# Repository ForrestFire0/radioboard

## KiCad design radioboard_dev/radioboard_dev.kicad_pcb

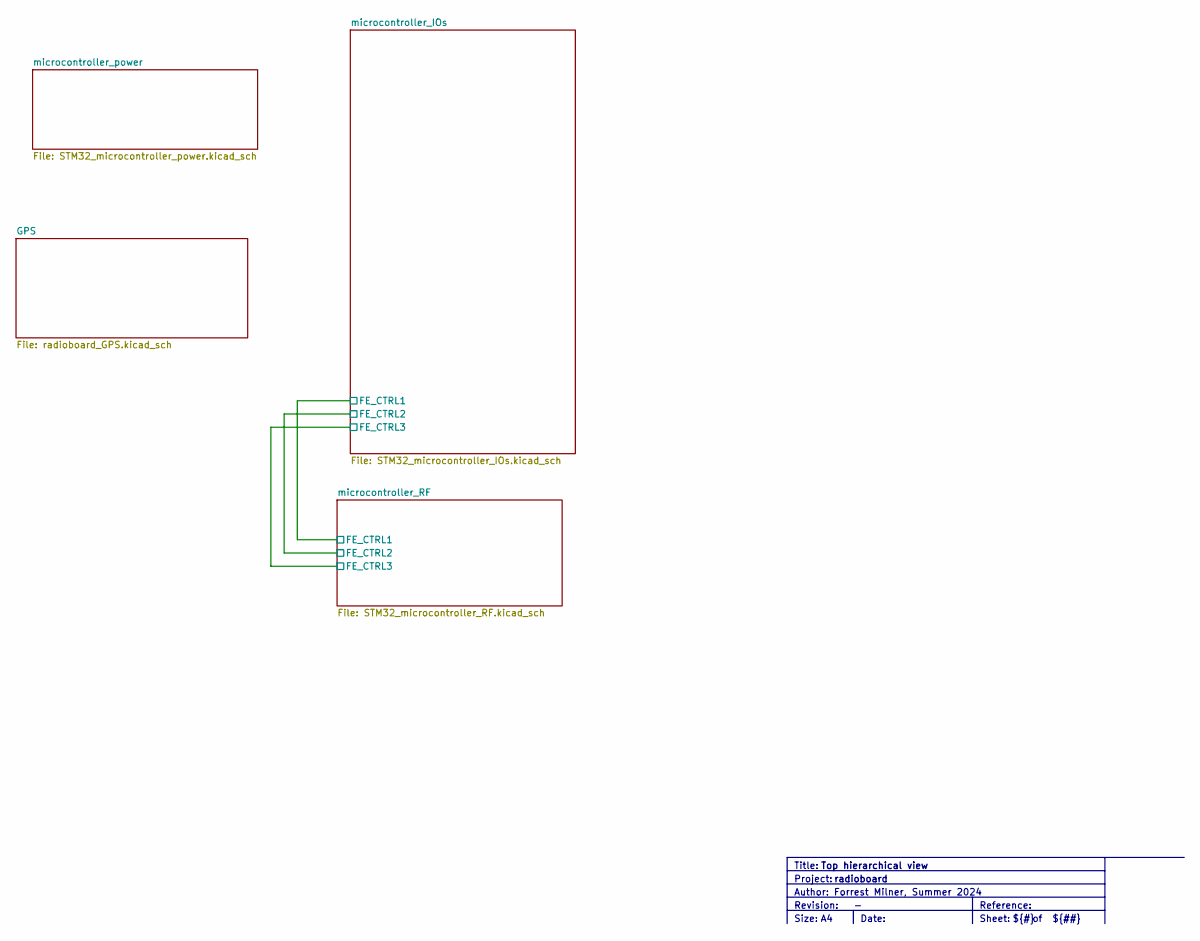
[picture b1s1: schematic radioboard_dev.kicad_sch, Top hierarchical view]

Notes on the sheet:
Size:
${TITLE}
Revision:
Title:
Sheet:
Date:
Reference:
${##}
Project:
radioboard
${#}
Author: Forrest Milner, Summer 2024

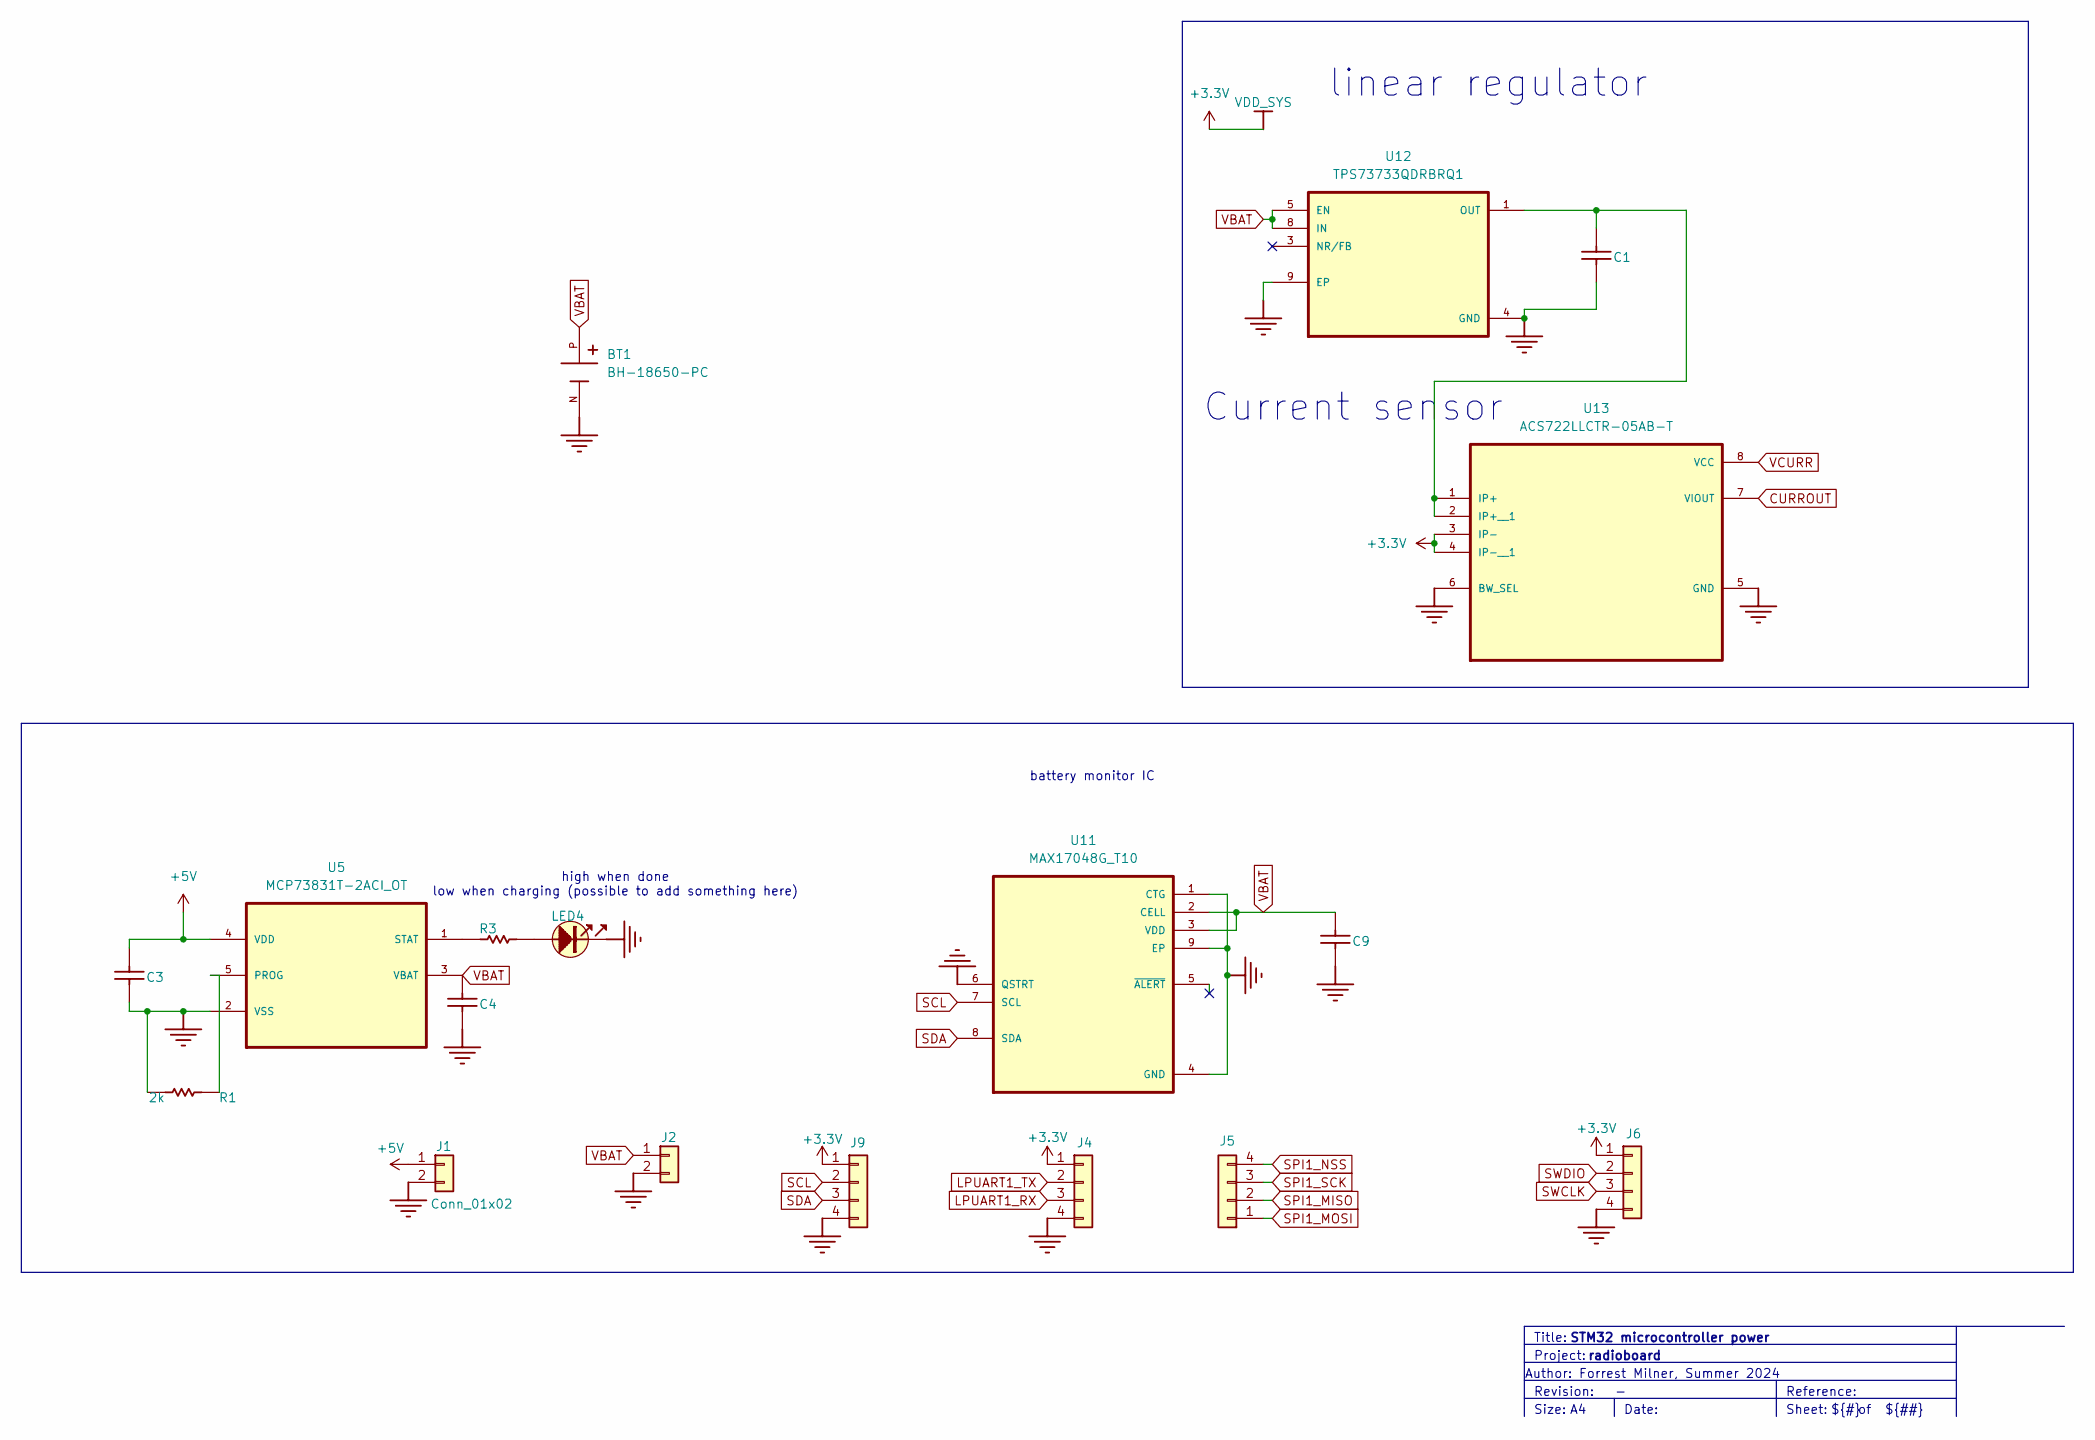
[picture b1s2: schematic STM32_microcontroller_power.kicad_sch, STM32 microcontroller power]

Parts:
BT1: BH-18650-PC; BAT_BH-18650-PC
C1, C3, C4: 4.7uF; C0603; PART_TYPE Capacitor
C9: 100nF; C0402; PART_TYPE Capacitor
J1, J2: Conn_01x02; PinHeader_1x02_P2.54mm_Vertical
J4, J5, J6, J9: Conn_01x04; PinHeader_1x04_P2.54mm_Vertical
LED4: LED_0603_OSRAM_LG-Q396-PS-35_GREEN_1A2K_H0P4
R1: 2k; R0402
R3: 270R; R0402
U5: MCP73831T-2ACI_OT; SOT95P280X145-5N
U11: MAX17048G_T10; SON50P200X200X80-9N
U12: TPS73733QDRBRQ1; IC_DRV8601DRBT
U13: ACS722LLCTR-05AB-T; SOIC127P600X175-8N

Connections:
+3.3V: J4.1, J6.1, J9.1, U13.3 (IP-), U13.4 (IP-__1); also elsewhere on the board
+5V: C3.2, J1.1, U5.4 (VDD)
CURROUT: U13.7 (VIOUT); also elsewhere on the board
GND: BT1.N, C1.1, C3.1, C4.1, C9.2, J1.2, J2.2, J4.4, J6.4, J9.4, LED4.2, R1.2, U5.2 (VSS), U11.1 (CTG), U11.4 (GND), U11.6 (QSTRT), U11.9 (EP), U12.4 (GND), U12.9 (EP), U13.5 (GND), U13.6 (BW_SEL); also elsewhere on the board
LPUART1_RX: J4.3; also elsewhere on the board
LPUART1_TX: J4.2; also elsewhere on the board
unnamed: LED4.1, R3.2
unnamed: R1.1, U5.5 (PROG)
unnamed: R3.1, U5.1 (STAT)
unnamed: C1.2, U12.1 (OUT), U13.1 (IP+), U13.2 (IP+__1)
SCL: J9.2, U11.7 (SCL); also elsewhere on the board
SDA: J9.3, U11.8 (SDA); also elsewhere on the board
SPI1_MISO: J5.2; also elsewhere on the board
SPI1_MOSI: J5.1; also elsewhere on the board
SPI1_NSS: J5.4; also elsewhere on the board
SPI1_SCK: J5.3; also elsewhere on the board
SWCLK: J6.3; also elsewhere on the board
SWDIO: J6.2; also elsewhere on the board
VBAT: BT1.P, C4.2, C9.1, J2.1, U5.3 (VBAT), U11.2 (CELL), U11.3 (VDD), U12.5 (EN), U12.8 (IN)
VCURR: U13.8 (VCC); also elsewhere on the board

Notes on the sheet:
Current sensor
Revision:
Sheet:
${TITLE}
Title:
Author: Forrest Milner, Summer 2024
${##}
radioboard
Date:
Reference:
high when done low when charging (possible to add something here)
battery monitor IC
Project:
${#}
Size:
linear regulator

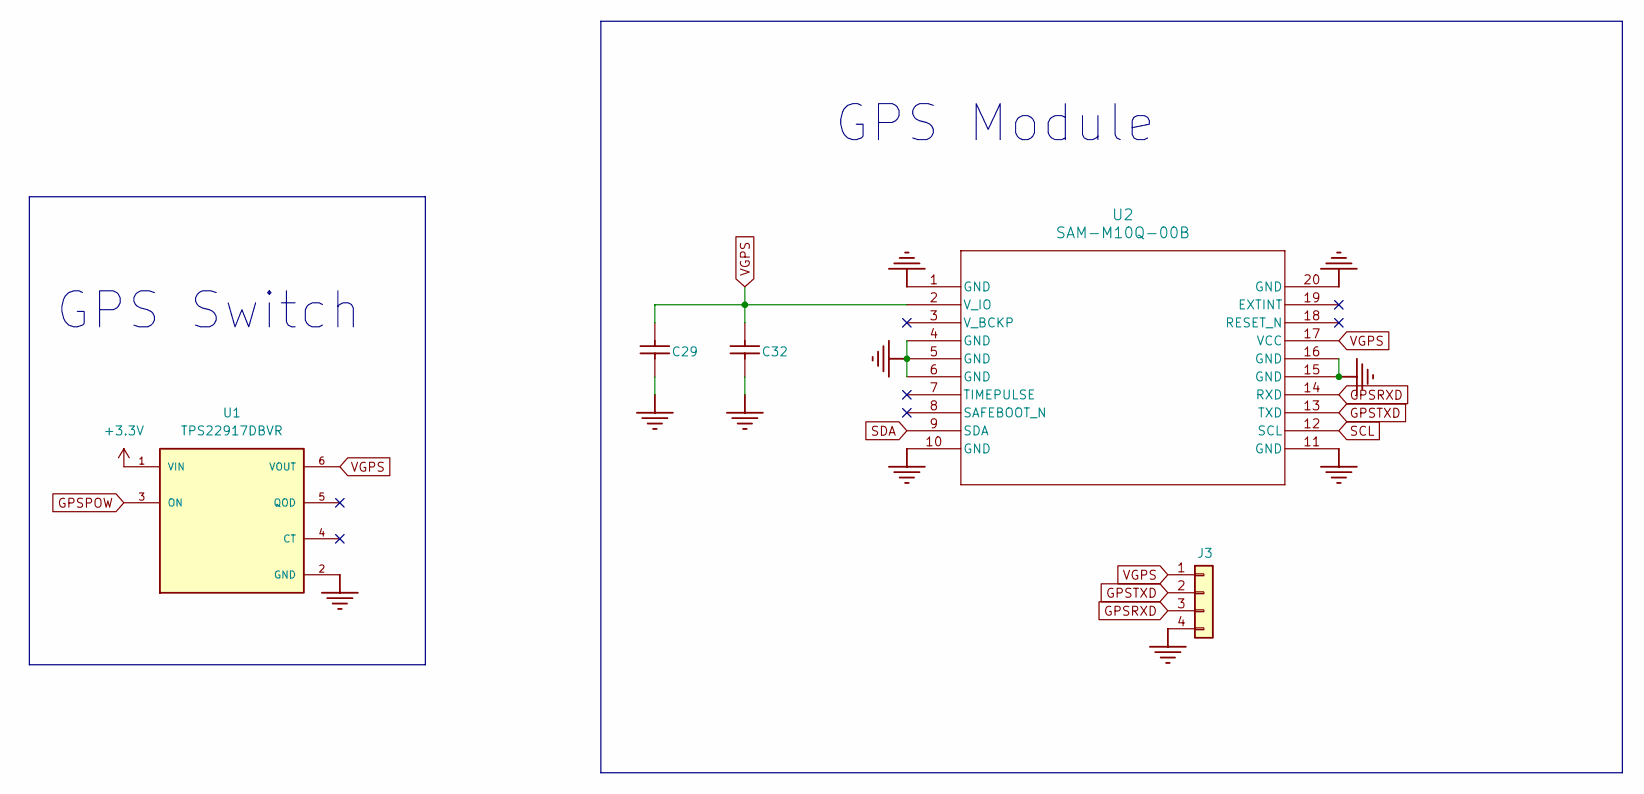
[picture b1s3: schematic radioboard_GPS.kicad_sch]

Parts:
C29: 4.7uF; C0603; PART_TYPE Capacitor
C32: 100nF; C0402; PART_TYPE Capacitor
J3: Conn_01x04; PinHeader_1x04_P2.54mm_Vertical
U1: TPS22917DBVR; SOT95P280X145-6N
U2: SAM-M10Q-00B; SAM-M10Q_UBL

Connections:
+3.3V: U1.1 (VIN); also elsewhere on the board
GND: C29.1, C32.2, J3.4, U1.2 (GND), U2.1 (GND), U2.4 (GND), U2.5 (GND), U2.6 (GND), U2.10 (GND), U2.11 (GND), U2.15 (GND), U2.16 (GND), U2.20 (GND); also elsewhere on the board
GPSPOW: U1.3 (ON); also elsewhere on the board
GPSRXD: J3.3, U2.14 (RXD)
GPSTXD: J3.2, U2.13 (TXD)
SCL: U2.12 (SCL); also elsewhere on the board
SDA: U2.9 (SDA); also elsewhere on the board
VGPS: C29.2, C32.1, J3.1, U1.6 (VOUT), U2.2 (V_IO), U2.17 (VCC)

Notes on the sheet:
GPS Module
GPS Switch

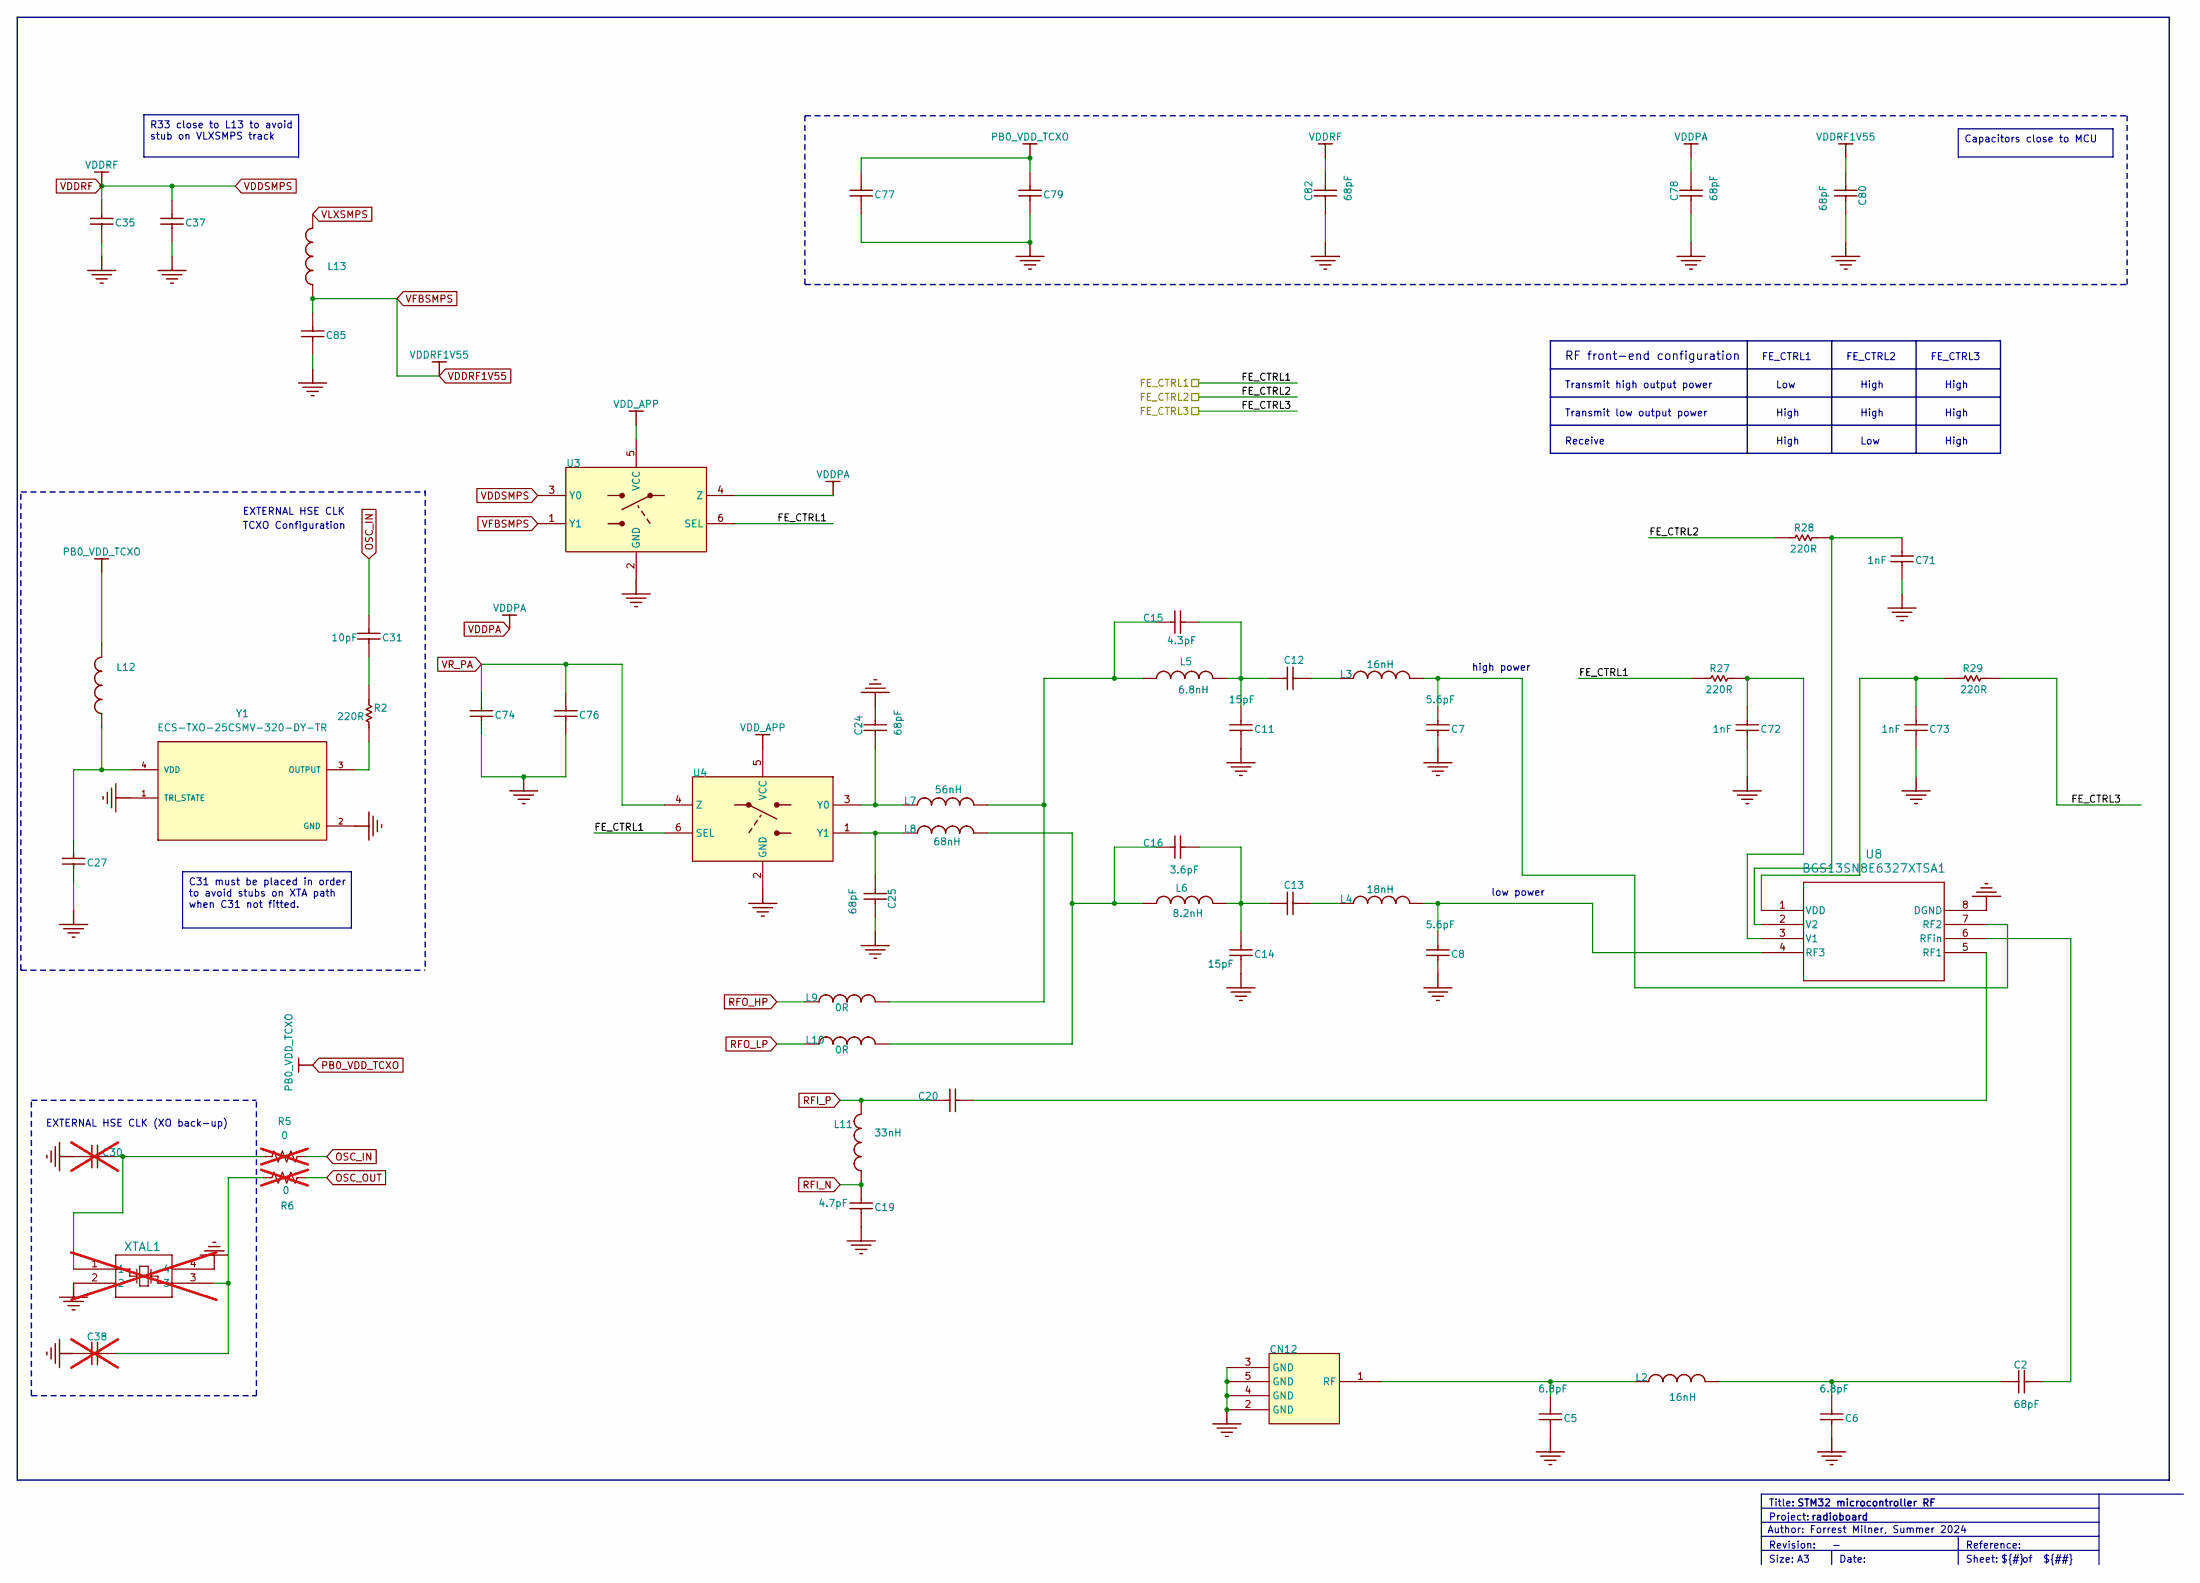
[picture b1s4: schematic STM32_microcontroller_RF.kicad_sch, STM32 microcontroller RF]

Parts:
C2, C24, C25, C76, C78, C80, C82: 68pF; C_0402_1005Metric
C5, C6: 6.8pF; C0402
C7, C8: 5.6pF; C_0402_1005Metric
C11, C14: 15pF; C_0402_1005Metric
C12, C13: 68pF; C_0402_1005Metric; PART_PREFERENCE Recommended
C15: 4.3pF; C_0402_1005Metric
C16, C20: 3.6pF; C_0402_1005Metric
C19: 4.7pF; C0402
C27: 220nF; C0402
C30, C38: 6.8pF; C0402; PART_TYPE Capacitor; not fitted
C31: 10pF; C0402
C35: 4.7uF; C0603; PART_TYPE Capacitor
C37: 100nF; C_0402_1005Metric
C71, C72, C73: 1nF; C0402
C74: 47nF; C0402
C77: 100nF; C0402
C79: 47pF; C0402
C85: 470nF; C0603
CN12: CON_SAMTEC_SMA-J-P-X-ST-EM1
L2, L3: 16nH; L_0402_1005Metric
L4: 18nH; L_0402_1005Metric
L5: 6.8nH; L_0402_1005Metric
L6: 8.2nH; L_0402_1005Metric
L7: 56nH; L_0402_1005Metric
L8: 68nH; L_0402_1005Metric
L9, L10: 0R; L_0402_1005Metric
L11: 33nH; IND_0402_MURATA_LQW15AN_H0P5
L12: L_0402_1005Metric
L13: 15µH; L_0805_2012Metric
R2, R27, R28, R29: 220R; R0402
R5, R6: 0; R_0402_1005Metric; not fitted
U3, U4: ICC_SOT886_XSON6
U8: BGS13SN8E6327XTSA1; TSNP-8-1_INF
XTAL1: NX2016SA-32M-EXS00A-CS06465; NX2016SA_NDK; not fitted
Y1: ECS-TXO-25CSMV-320-DY-TR; OSC_ECS-TXO-25CSMV-320-DY-TR

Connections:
/microcontroller_RF/FE_CTRL1: R27.2, U3.6 (SEL), U4.6 (SEL); also elsewhere on the board
/microcontroller_RF/FE_CTRL2: R28.2; also elsewhere on the board
/microcontroller_RF/FE_CTRL3: R29.1; also elsewhere on the board
GND: C5.1, C6.1, C7.1, C8.1, C11.1, C14.1, C19.1, C24.2, C25.2, C27.1, C30.1, C35.1, C37.2, C38.1, C71.1, C72.1, C73.1, C74.1, C76.1, C77.2, C78.1, C79.1, C80.2, C82.1, C85.1, CN12.2 (GND), CN12.3 (GND), CN12.4 (GND), CN12.5 (GND), U3.2 (GND), U4.2 (GND), U8.8 (DGND), XTAL1.2, XTAL1.4, Y1.1 (TRI_STATE), Y1.2 (GND); also elsewhere on the board
unnamed: C2.1, C6.2, L2.2
unnamed: C11.2, C12.1, C15.2, L5.2
unnamed: C12.2, L3.1
unnamed: C13.1, C14.2, C16.2, L6.2
unnamed: C13.2, L4.1
unnamed: C15.1, L5.1, L7.2, L9.2
unnamed: C16.1, L6.1, L8.2, L10.2
unnamed: C30.2, R5.1, XTAL1.1
unnamed: C31.1, R2.2
unnamed: C38.2, R6.2, XTAL1.3
unnamed: C5.2, CN12.1 (RF), L2.1
unnamed: C24.1, L7.1, U4.3 (Y0)
unnamed: C25.1, L8.1, U4.1 (Y1)
unnamed: C20.2, U8.5 (RF1)
unnamed: C7.2, L3.2, U8.7 (RF2)
unnamed: C8.2, L4.2, U8.4 (RF3)
unnamed: C2.2, U8.6 (RFin)
unnamed: C72.2, R27.1, U8.3 (V1)
unnamed: C71.2, R28.1, U8.2 (V2)
unnamed: C73.2, R29.2, U8.1 (VDD)
unnamed: R2.1, Y1.3 (OUTPUT)
unnamed: C27.2, L12.1, Y1.4 (VDD)
OSC_IN: C31.2, R5.2; also elsewhere on the board
OSC_OUT: R6.1; also elsewhere on the board
PB0_VDD_TCXO: C77.1, C79.2, L12.2; also elsewhere on the board
RFI_N: C19.2, L11.1; also elsewhere on the board
RFI_P: C20.1, L11.2; also elsewhere on the board
RFO_HP: L9.1; also elsewhere on the board
RFO_LP: L10.1; also elsewhere on the board
VDDPA: C78.2, U3.4 (Z); also elsewhere on the board
VDDRF: C35.2, C37.1, C82.2, U3.3 (Y0); also elsewhere on the board
VDDRF1V55: C80.1, C85.2, L13.1, U3.1 (Y1); also elsewhere on the board
VDD_APP: U3.5 (VCC), U4.5 (VCC)
VLXSMPS: L13.2; also elsewhere on the board
VR_PA: C74.2, C76.2, U4.4 (Z); also elsewhere on the board

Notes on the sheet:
R33 close to L13 to avoid stub on VLXSMPS track
C31 must be placed in order to avoid stubs on XTA path when C31 not fitted.
Capacitors close to MCU
Title:
${#}
High
Low
RF front-end configuration
Receive
Sheet:
Transmit low output power
low power
Transmit high output power
FE_CTRL3
FE_CTRL2
FE_CTRL1
Reference:
Author: Forrest Milner, Summer 2024
${TITLE}
Date:
Revision:
high power
Size:
Project:
${##}
radioboard
EXTERNAL HSE CLK (XO back-up)
TCXO Configuration
EXTERNAL HSE CLK

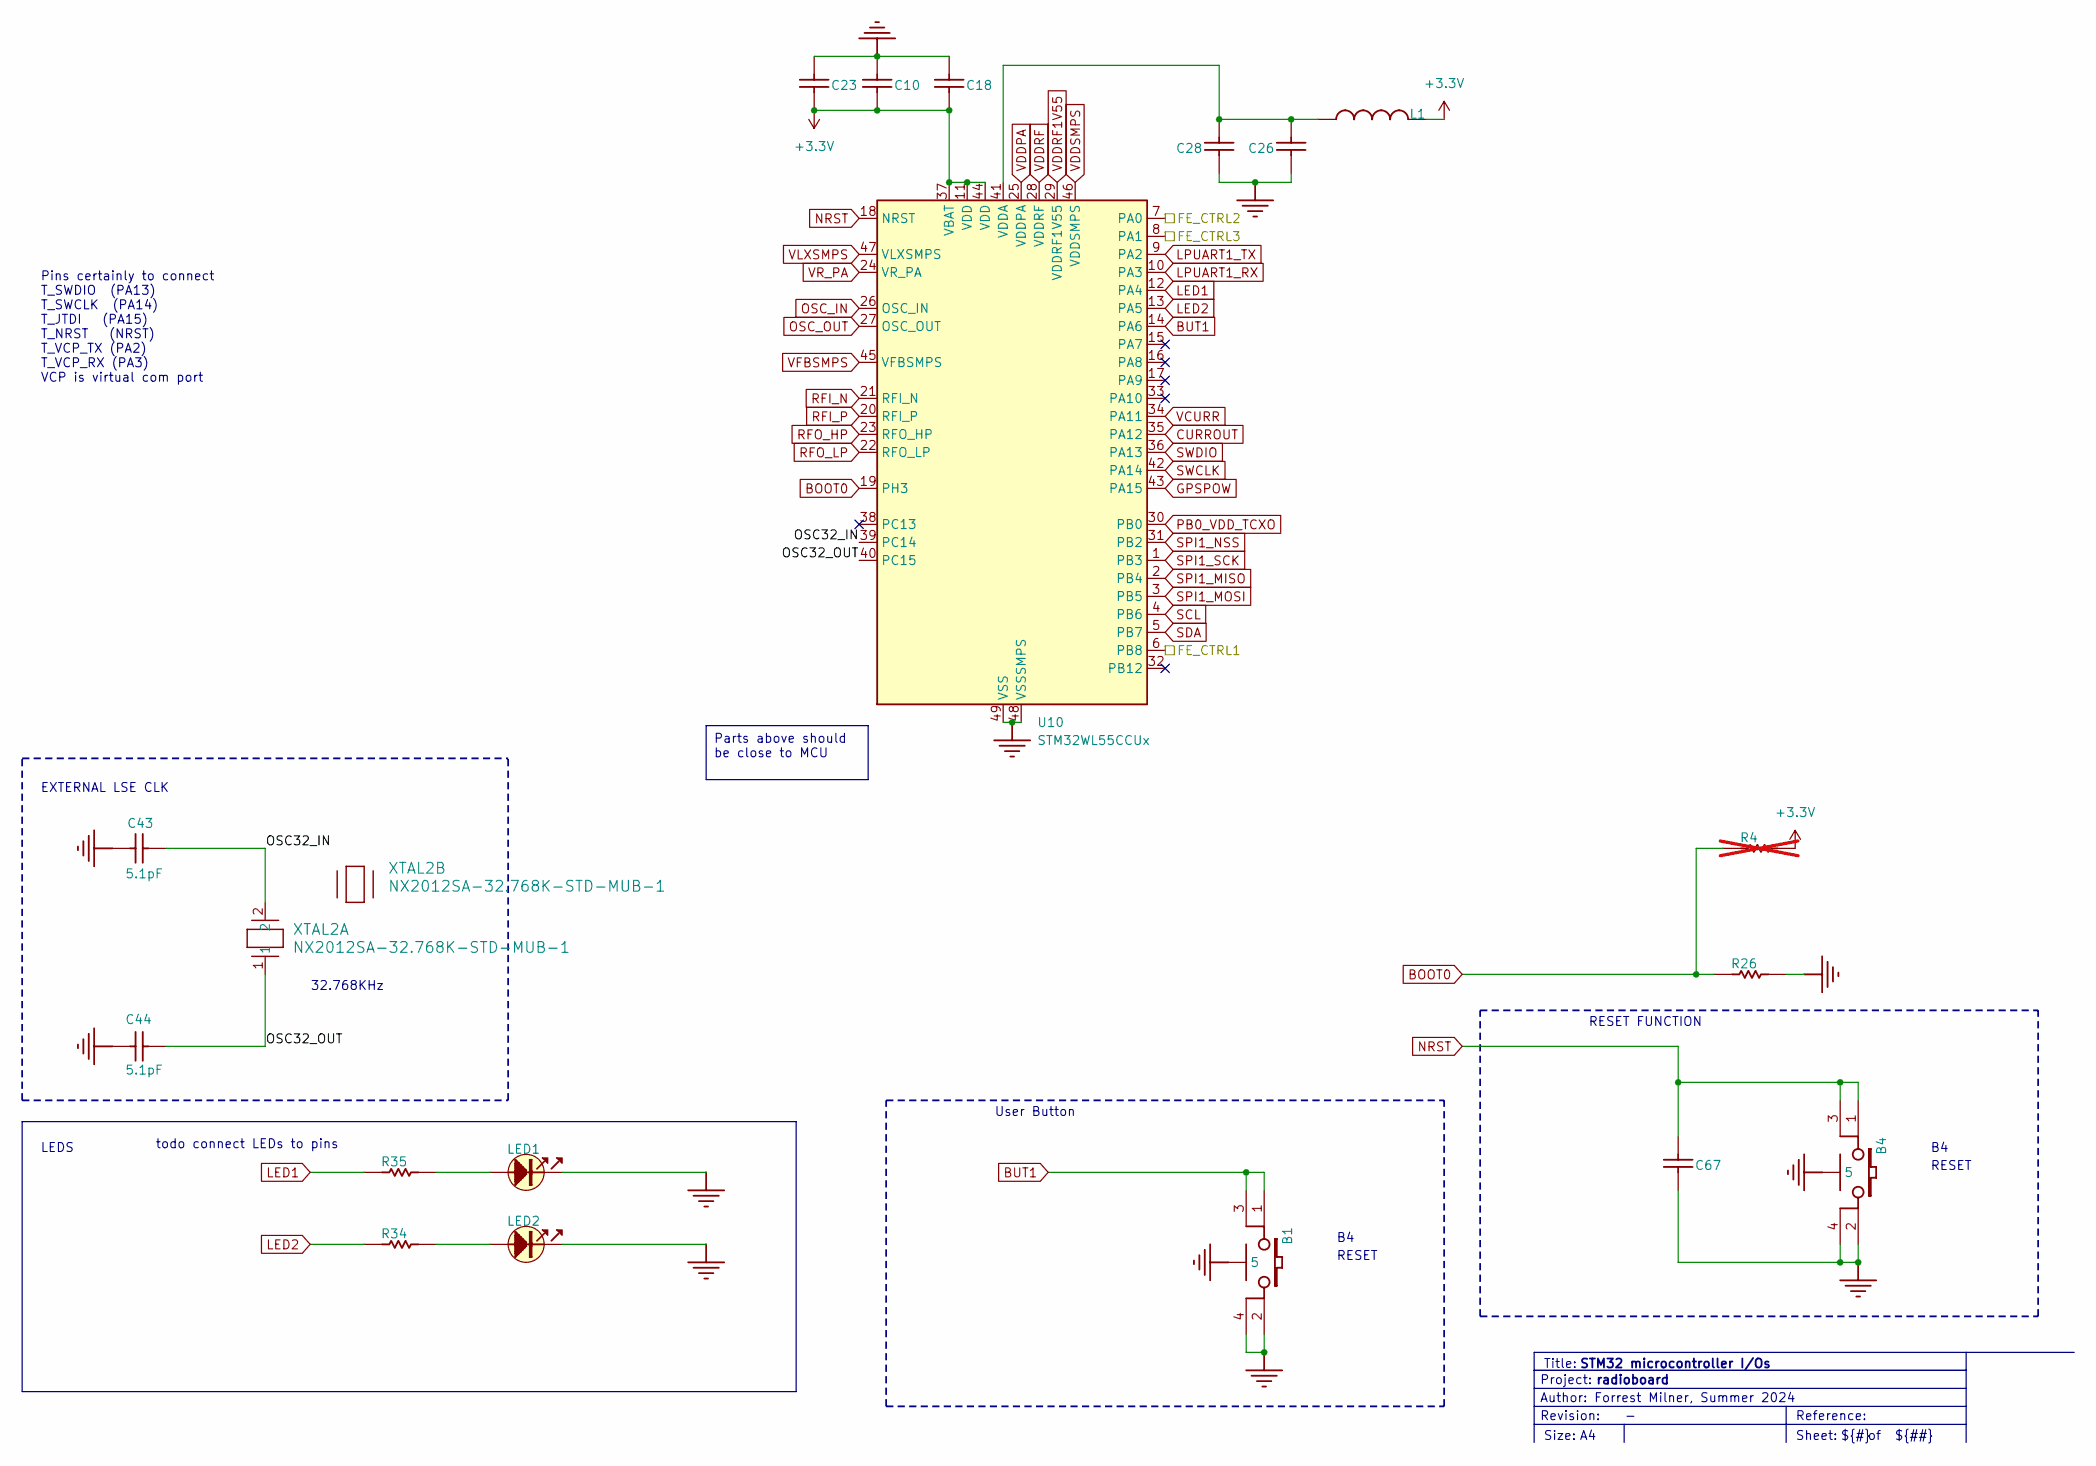
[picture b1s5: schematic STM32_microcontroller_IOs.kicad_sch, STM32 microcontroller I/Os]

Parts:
B1, B4: SWI_C&K_Y78B23110FP__ITT_KMR231GLFS
C10, C18, C23, C28, C67: 100nF; C0402; PART_TYPE Capacitor
C26: 4.7uF; C0603; PART_TYPE Capacitor
C43, C44: 5.1pF; C0402
L1: L_0603_1608Metric; PART_TYPE Inductor
LED1: LED_0603_OSRAM_LG-Q396-PS-35_GREEN_1A2K_H0P4
LED2: LED_0603_VISHAY_VLMS1300-GS08_RED_1A2K_H0P8
R4: 10k; R0603; not fitted
R26: 10k; R0603
R34: 360R; R0402
R35: 270R; R0402
U10: STM32WL55CCUx; QFN-48-1EP_7x7mm_P0.5mm_EP5.6x5.6mm
XTAL2: NX2012SA-32.768K-STD-MUB-1; XTAL_NX2012SA_NDK

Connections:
+3.3V: C10.1, C18.1, C23.1, L1.1, R4.1, U10.11 (VDD), U10.37 (VBAT), U10.44 (VDD); also elsewhere on the board
/microcontroller_IOs/OSC32_IN: C43.1, U10.39 (PC14), XTAL2.2
/microcontroller_IOs/OSC32_OUT: C44.1, U10.40 (PC15), XTAL2.1
/microcontroller_RF/FE_CTRL1: U10.6 (PB8); also elsewhere on the board
/microcontroller_RF/FE_CTRL2: U10.7 (PA0); also elsewhere on the board
/microcontroller_RF/FE_CTRL3: U10.8 (PA1); also elsewhere on the board
BOOT0: R4.2, R26.2, U10.19 (PH3)
BUT1: B1.1, B1.3, U10.14 (PA6)
CURROUT: U10.35 (PA12); also elsewhere on the board
GND: B1.2, B1.4, B1.5, B4.2, B4.4, B4.5, C10.2, C18.2, C23.2, C26.1, C28.1, C43.2, C44.2, C67.1, LED1.2, LED2.2, R26.1, U10.48 (VSSSMPS), U10.49 (VSS); also elsewhere on the board
GPSPOW: U10.43 (PA15); also elsewhere on the board
LED1: R35.1, U10.12 (PA4)
LED2: R34.1, U10.13 (PA5)
LPUART1_RX: U10.10 (PA3); also elsewhere on the board
LPUART1_TX: U10.9 (PA2); also elsewhere on the board
NRST: B4.1, B4.3, C67.2, U10.18 (NRST)
unnamed: LED1.1, R35.2
unnamed: LED2.1, R34.2
unnamed: C26.2, C28.2, L1.2, U10.41 (VDDA)
OSC_IN: U10.26 (OSC_IN); also elsewhere on the board
OSC_OUT: U10.27 (OSC_OUT); also elsewhere on the board
PB0_VDD_TCXO: U10.30 (PB0); also elsewhere on the board
RFI_N: U10.21 (RFI_N); also elsewhere on the board
RFI_P: U10.20 (RFI_P); also elsewhere on the board
RFO_HP: U10.23 (RFO_HP); also elsewhere on the board
RFO_LP: U10.22 (RFO_LP); also elsewhere on the board
SCL: U10.4 (PB6); also elsewhere on the board
SDA: U10.5 (PB7); also elsewhere on the board
SPI1_MISO: U10.2 (PB4); also elsewhere on the board
SPI1_MOSI: U10.3 (PB5); also elsewhere on the board
SPI1_NSS: U10.31 (PB2); also elsewhere on the board
SPI1_SCK: U10.1 (PB3); also elsewhere on the board
SWCLK: U10.42 (PA14); also elsewhere on the board
SWDIO: U10.36 (PA13); also elsewhere on the board
VCURR: U10.34 (PA11); also elsewhere on the board
VDDPA: U10.25 (VDDPA); also elsewhere on the board
VDDRF: U10.28 (VDDRF), U10.46 (VDDSMPS); also elsewhere on the board
VDDRF1V55: U10.29 (VDDRF1V55), U10.45 (VFBSMPS); also elsewhere on the board
VLXSMPS: U10.47 (VLXSMPS); also elsewhere on the board
VR_PA: U10.24 (VR_PA); also elsewhere on the board

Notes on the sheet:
Parts above should be close to MCU
${TITLE}
32.768KHz
Reference:
Size:
${#}
Title:
EXTERNAL LSE CLK
RESET FUNCTION
LEDS
Project:
radioboard
Author: Forrest Milner, Summer 2024
${##}
RESET
Revision:
Pins certainly to connect T_SWDIO (PA13) T_SWCLK (PA14) T_JTDI (PA15) T_NRST (NRST) T_VCP_TX (PA2) T_VCP_RX (PA3) VCP is virtual com port
todo connect LEDs to pins
Sheet:
User Button

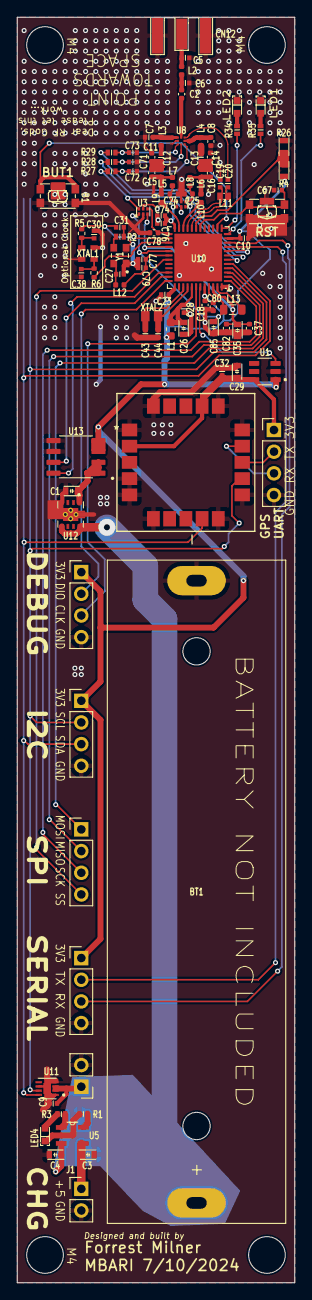
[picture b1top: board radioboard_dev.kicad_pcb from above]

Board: 4 copper layers, 32.5 x 148.2 mm, 98 parts (0 on the bottom side), 72 nets.

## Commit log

2024-06-20 gitignore
2024-06-20 kicad xfer
2024-07-02 altium, dev, original
2024-07-08 added components
2024-07-08 finish schematic and clear pcb
2024-07-08 footprints
2024-07-09 added gps
2024-07-09 all footprints done
2024-07-09 pcb snapshot
2024-07-09 changed parts to 400MHz version
2024-07-10 done for day
2024-07-10 roughly placed
2024-07-10 almost done!!!
2024-07-10 routing minus ground planes complete
2024-07-10 pre mass edit of footprints
2024-07-10 basically done
2024-07-11 DRC stitching
2024-07-11 bom changes
2024-07-16 datasgeers added...
2024-07-17 finished bom
2024-07-17 removed HW20
2024-07-17 rotate
2024-08-12 last commit
